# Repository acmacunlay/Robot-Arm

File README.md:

# robot-arm

## Developers:
- Achilles C. Macunlay
- Jon Thaddeus F. Laguitao

## Description:

This project is a simple Arduino-based robot arm that can be controlled via Bluetooth 
using an Android app.

## Files:

- **RobotArm.aia** - Use this if you want to modify the Android app. This can be modified with MIT App Inventor or Kodular (preferably Kodular).

- **RobotArm.apk** - This is the ready-to-install Android app to control the arm.

- **RobotArm.ino** - Use this if you want to calibrate or modify the robot arm's configurations. This can be modified with Arduino IDE (preferably).

## References:

- [3D Models](https://howtomechatronics.com/tutorials/arduino/diy-arduino-robot-arm-with-smartphone-control/)
- [Code](https://howtomechatronics.com/projectsarduino-robot-arm-and-mecanum-wheels-platform-automatic-operation/)

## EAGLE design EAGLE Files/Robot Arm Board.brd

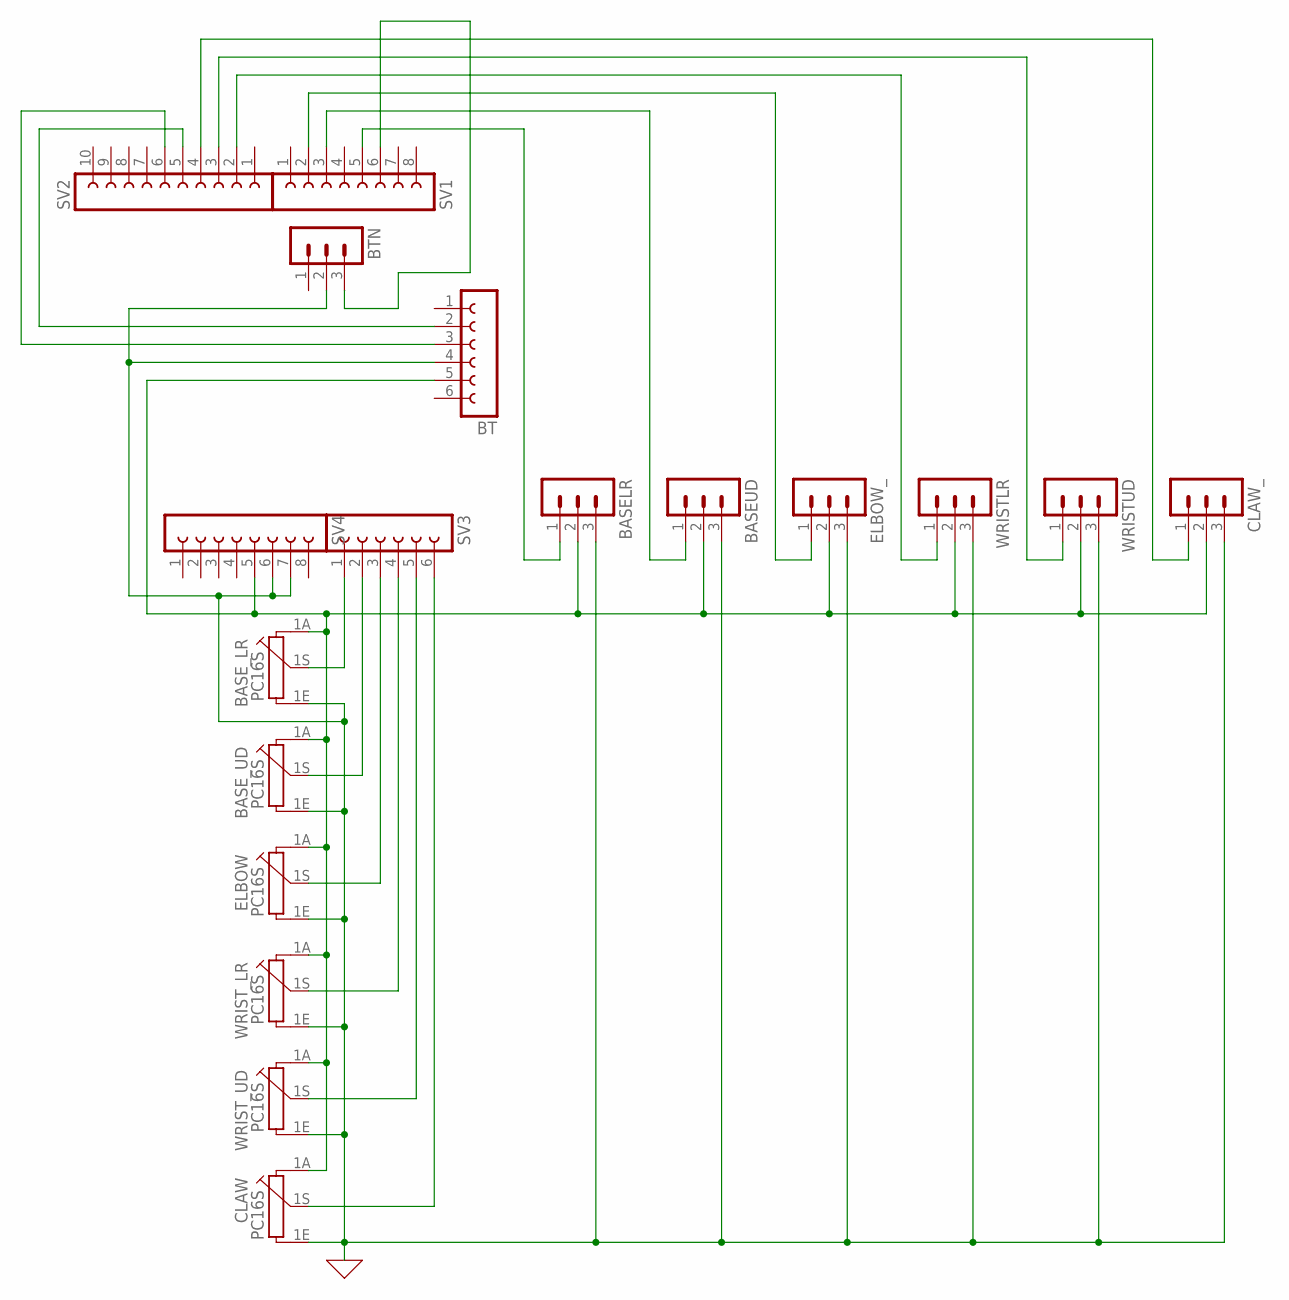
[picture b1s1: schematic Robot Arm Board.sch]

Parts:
BASELR: MA03-1
BASEUD: MA03-1
BASE_LR: PC16S
BASE_UD: PC16S
BT: FE06-1; FE06
BTN: MA03-1
CLAW: PC16S
CLAW_: MA03-1
ELBOW: PC16S
ELBOW_: MA03-1
SV1, SV4: FE08-1; FE08
SV2: FE10-1; FE10
SV3: FE06-1; FE06
WRISTLR: MA03-1
WRISTUD: MA03-1
WRIST_LR: PC16S
WRIST_UD: PC16S

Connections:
GND: BASELR.3, BASEUD.3, BASE_LR.1E, BASE_UD.1E, BT.4, BTN.2, CLAW.1E, CLAW_.3, ELBOW.1E, ELBOW_.3, SV4.6, SV4.7, WRISTLR.3, WRISTUD.3, WRIST_LR.1E, WRIST_UD.1E
unnamed: BASE_LR.1S, SV3.1
unnamed: BASE_UD.1S, SV3.2
unnamed: ELBOW.1S, SV3.3
unnamed: SV3.4, WRIST_LR.1S
unnamed: SV3.5, WRIST_UD.1S
unnamed: CLAW.1S, SV3.6
unnamed: SV2.3, WRISTUD.1
unnamed: BASELR.1, SV1.5
unnamed: BASEUD.1, SV1.3
unnamed: ELBOW_.1, SV1.2
unnamed: SV2.2, WRISTLR.1
unnamed: BASELR.2, BASEUD.2, BASE_LR.1A, BASE_UD.1A, BT.5, CLAW.1A, CLAW_.2, ELBOW.1A, ELBOW_.2, SV4.5, WRISTLR.2, WRISTUD.2, WRIST_LR.1A, WRIST_UD.1A
unnamed: CLAW_.1, SV2.4
unnamed: BTN.3, SV1.6
unnamed: BT.2, SV2.5
unnamed: BT.3, SV2.6

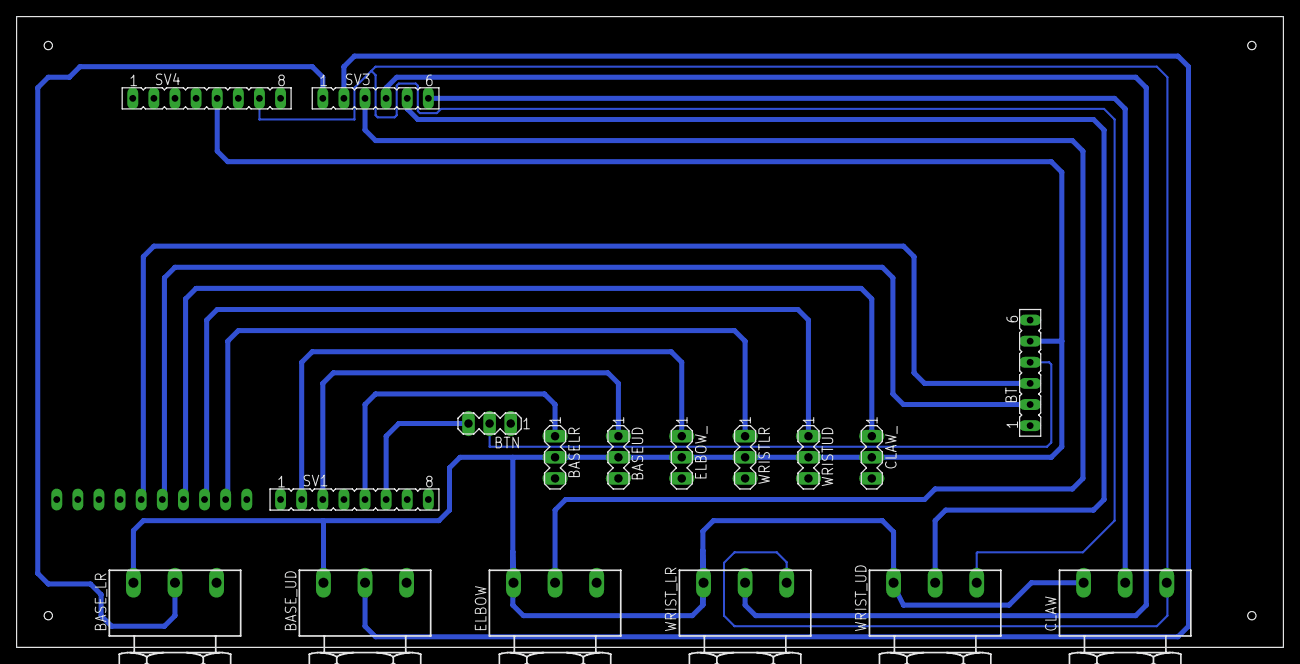
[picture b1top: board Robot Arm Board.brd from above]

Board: 2 copper layers, 152.4 x 75.9 mm, 18 parts (1 on the bottom side), 17 nets.

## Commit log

2020-06-20 2020-06-20-new-README
    Wrote the README.
2020-06-20 2020-06-20-edit-README
    additional info for README.md
2020-06-20 2020-06-20-edit-RobotArm
    edited comments
2020-06-20 2020-06-20-new-Models
    added the DWG and STL files
2021-02-25 2021-02-25 2301
    Edited README.md
2021-03-23 2021-03-23 1520
